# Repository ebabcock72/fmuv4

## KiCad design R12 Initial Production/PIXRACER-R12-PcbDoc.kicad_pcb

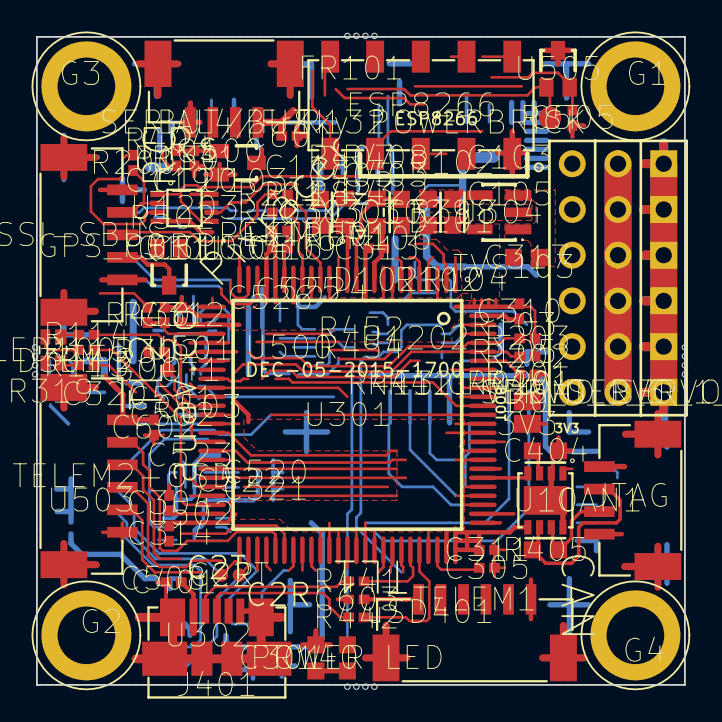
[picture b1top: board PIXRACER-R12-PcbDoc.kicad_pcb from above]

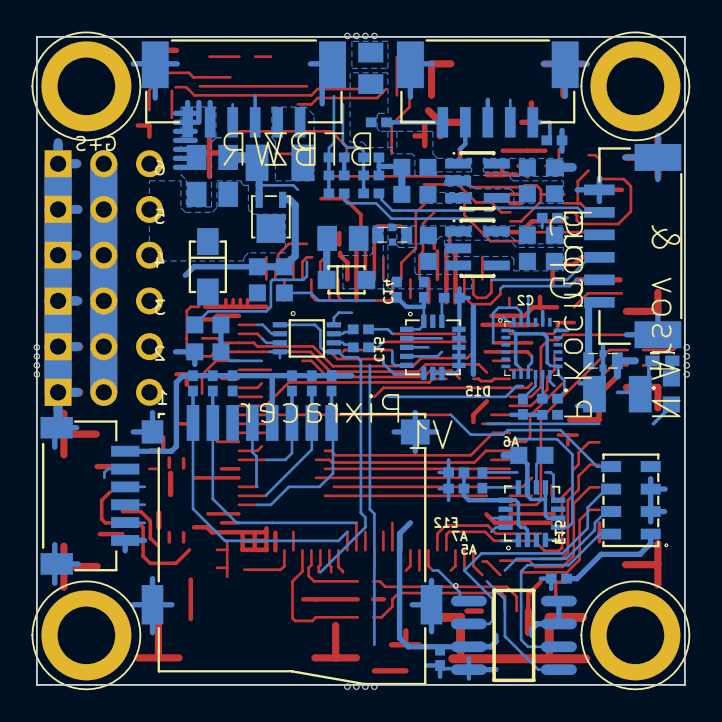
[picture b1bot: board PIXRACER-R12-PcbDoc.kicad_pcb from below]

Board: 4 copper layers, 36.0 x 36.0 mm, 134 parts (66 on the bottom side), 127 nets.

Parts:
3V3: 3V3; PAD1
B0: B0; PAD1
BOOT1: BOOT1; PAD1
BUT/BUZ: BUT/BUZ; Molex_Clik_1.25_5H
C2R: C2R; PAD1
C2T: C2T; PAD1
C103: C103; 0805A
C105: C105; 0805A
C118: C118; 0603A
C119: C119; 0603A
C120: C120; 0603A
C301: C301; 0402A
C302: C302; 0603A
C303: C303; 0603A
C304: C304; 0402A
C305: C305; 0402A
C310: C310; 0402A
C311: C311; 0402A
C312: C312; 0402A
C313: C313; 0402A
C314: C314; 0402A
C315: C315; 0402A
C316: C316; 0402A
C317: C317; 0603A
C319: C319; 0603A
C320: C320; 1206A
C401: C401; 0402A
C402: C402; 0402A
C403: C403; 0402A
C404: C404; 0603A
C405: C405; 0402A
C501: C501; 0402A
C502: C502; 0402A
C503: C503; 0402A
C505: C505; 0402A
C508: C508; 0402A
C509: C509; 0603A
C510: C510; 0603A
C511: C511; 0603A
C520: C520; 0402A
C521: C521; 0402A
C522: C522; 0402A
C523: C523; 0603A
C524: C524; 0402A
C525: C525; 0402A
C526: C526; 0402A
C601: C601; 0402A
C602: C602; 0402A
C603: C603; 0402A
CAN1: CAN1; Molex_1.25_click_4
D101: D101; pmeg2020cp
D102: D102; SOD323F
D301: D301; SOD-523
EMI201: EMI201; EMI_KNH16_0603
EMI501: EMI501; EMI_KNH16_0603
ESP8266: ESP8266; 2.54MM_10PIN_SMD
FR101: FR101; 0805A
FR102: FR102; 1206A
FR106: FR106; 0805A
G1: G1; SMT_PAD_ROUND
G2: G2; SMT_PAD_ROUND
G3: G3; SMT_PAD_ROUND
G4: G4; SMT_PAD_ROUND
GND_SERVO_1_6: GND_SERVO_1_6; HDR1X6
GPS_PORT: GPS_PORT; Molex_Clok_1.25_6H
J401: J401; USBmicro_B
JTAG: JTAG; SM06B-SRSH-TB
LED100: LED100; LTST-C19HE1WT
POWER LED: POWER LED; 0603A
POWERBRICK: POWERBRICK; Molex_Clok_1.25_6H
PPM-RSSI-SBUS-SPEKTRUM: PPM-RSSI-SBUS-SPEKTRUM; Molex_Clik_1.25_5H
Q100: Q100; 2N7002-SOT323
Q101: Q101; 2N7002-SOT323
R102: R102; 0603A
R103: R103; 0603A
R104: R104; 0603A
R105: R105; 0603A
R113: R113; 0402A
R114: R114; 0402A
R115: R115; 0402A
R118: R118; 0603A
R130: R130; 0402A
R131: R131; 0402A
R132: R132; 0402A
R140: R140; 0603A
R200: R200; 0402A
R201: R201; 0402A
R202: R202; 0402A
R203: R203; 0402A
R301: R301; 0402A
R302: R302; 0402A
R318: R318; 0603A
R319: R319; 0603A
R401: R401; 0402A
R403: R403; 0402A
R404: R404; 0402A
R405: R405; 0603A
R407: R407; 0402A
R408: R408; 0402A
R410: R410; 0402A
R411: R411; 0402A
R412: R412; 0402A
R413: R413; 0402A
R422: R422; 0402A
R423: R423; 0402A
R430: R430; 0402A
R431: R431; 0402A
R441: R441; 0402A
R442: R442; 0402A
R452: R452; 0402A
R454: R454; 0402A
R502: R502; 0402A
RST: RST; PAD1
SERIAL4/FrSky: SERIAL4/FrSky; Molex_1.25_click_4
SERVO_1_6: SERVO_1_6; HDR1X6
TELEM1: TELEM1; Molex_Clok_1.25_6H
TELEM2+OSD: TELEM2+OSD; Molex_Clok_1.25_6H
TVS103: TVS103; SOD123F
U10: U10; 8DFN_3x3
U103: U103; SOT23-5
U301: U301; LQFP100_L
U302: U302; SO-8_N
U304: U304; SOT23-5
U500: U500; HCLGA-16L
U501: U501; MPU6500-9250
U502: U502; HMC5883L
U503: U503; MS5611
U504: U504; SOT23-5
U505: U505; SOT-323
U1202: U1202; DCU(SM-8)
U1203: U1203; DCU(SM-8)
VDD_SERVO_1_6: VDD_SERVO_1_6; HDR1X6
X301: X301; Crystal_2.5x2
uSD401: uSD401; MicroSD_China_01

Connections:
8266_CTS: ESP8266.10, U301.41
8266_GPIO0: ESP8266.6, U301.1
8266_GPIO2: ESP8266.4, U301.90
8266_PD: ESP8266.3, U301.4
8266_RST: ESP8266.5, U301.5
8266_RTS: ESP8266.9, U301.67
20608_CS: U301.9, U500.5
20608_DRDY: U301.8, U500.6
ALARM: R130.2, U301.77
BARO_CS: U301.88, U503.5
BATT_CURRENT_SENS: R422.1, U301.26
BATT_VOLT_SENS: R423.1, U301.25
BOOT0: B0.1, R301.1, U301.94
BUZZER+: BUT/BUZ.5, R132.1
BUZZER-: BUT/BUZ.4, Q100.1
CAN1_RX: U10.4, U301.81
CAN1_TX: U10.1, U301.82
CAN2_RX: C2R.1, U301.51
CAN2_TX: C2T.1, U301.52
FMU_CH1: SERVO_1_6.1, U301.45
FMU_CH2: SERVO_1_6.2, U301.44
FMU_CH3: SERVO_1_6.3, U301.42
FMU_CH4: SERVO_1_6.4, U301.40
FMU_CH5: SERVO_1_6.5, U301.60
FMU_CH6: SERVO_1_6.6, U301.61
FMU_I2C1_SCL: GPS_PORT.4, R202.2, U301.95
FMU_I2C1_SDA: GPS_PORT.5, R203.2, U301.96
FMU_LED_BLUE: R113.1, U301.89
FMU_LED_GREEN: R114.1, U301.36
FMU_LED_RED: R115.1, U301.48
FMU_RC_INPUT: U301.35, U301.64, U1203.7
FMU_RC_OUTPUT: U301.63, U1203.6
FMU_SWCLK: JTAG.5, U301.76
FMU_SWDIO: JTAG.4, U301.72
FMU_UART7_RX: JTAG.3, U301.38
FMU_UART7_TX: JTAG.2, U301.39
FMU_USART1_RX: ESP8266.1, U301.93
FMU_USART1_TX: ESP8266.8, U301.92
FMU_USART2_CTS: TELEM1.4, U301.84
FMU_USART2_RTS: TELEM1.5, U301.85
FMU_USART2_RX: TELEM1.3, U301.87
FMU_USART2_TX: TELEM1.2, U301.86
FMU_USART3_CTS: TELEM2+OSD.4, U301.58
FMU_USART3_RTS: TELEM2+OSD.5, U301.59
FMU_USART3_RX: TELEM2+OSD.3, U301.56
FMU_USART3_TX: TELEM2+OSD.2, U301.55
FMU_USART4_RX: GPS_PORT.3, U301.24
FMU_USART4_TX: GPS_PORT.2, U301.23
FMU_USART8_RX: U301.97, U1202.3
FMU_USART8_TX: U301.98, U1202.2
FMU_VBAT: C320.2, D301.2, U301.6
FMU_VDD_3V3: 3V3.1, BUT/BUZ.3, C301.2, C310.2, C311.2, C312.2, C313.2, C314.2, C315.2, C316.2, C319.2, C402.1, C505.2, JTAG.1, LED100.4, R202.1, R203.1, R318.2, R319.1, R401.2, R410.2, R411.2, R412.2, R413.2, U10.5, U301.11, U301.19, U301.21, U301.22, U301.28, U301.50, U301.75, U301.100, U302.3, U302.7, U302.8, U304.5, U505.2, U1202.8, U1203.8, uSD401.4
FRAM_CS: U301.57, U302.1
FRAM_MISO: U301.53, U302.2, U503.6
FRAM_MOSI: U301.54, U302.5, U503.7
FRAM_SCK: U301.47, U302.6, U503.8
FRSKY_IN: R454.1, SERIAL4/FrSky.3
FRSKY_INV: U301.69, U1202.1, U1202.5
FRSKY_OUT: R452.1, SERIAL4/FrSky.2
GND: BUT/BUZ.GND, C103.1, C105.1, C118.1, C119.1, C120.1, C301.1, C302.1, C303.1, C304.2, C305.2, C310.1, C311.1, C312.1, C313.1, C314.1, C315.1, C316.1, C317.1, C319.1, C320.1, C401.1, C402.2, C403.2, C404.1, C405.2, C501.1, C502.1, C503.1, C505.1, C508.1, C509.1, C510.1, C511.1, C520.1, C521.1, C523.1, C524.1, C525.1, C526.1, C601.2, C602.2, C603.2, CAN1.4, CAN1.GND, EMI201.3, EMI201.4, EMI501.3, EMI501.4, ESP8266.2, G1.1, G2.1, G3.1, G4.1, GND_SERVO_1_6.1, GND_SERVO_1_6.2, GND_SERVO_1_6.3, GND_SERVO_1_6.4, GND_SERVO_1_6.5, GND_SERVO_1_6.6, GPS_PORT.6, GPS_PORT.GND, J401.5, J401.6, J401.7, JTAG.6, JTAG.GND, POWERBRICK.5, POWERBRICK.6, POWERBRICK.GND, PPM-RSSI-SBUS-SPEKTRUM.5, PPM-RSSI-SBUS-SPEKTRUM.GND, Q100.2, R104.1, R105.2, R118.1, R131.2, R140.1, R301.2, R302.1, R318.1, R404.2, R407.2, R408.2, R431.2, R502.1, SERIAL4/FrSky.4, SERIAL4/FrSky.GND, TELEM1.6, TELEM1.GND, TELEM2+OSD.6, TELEM2+OSD.GND, TVS103.1, U10.2, U10.8, U10.EP, U103.2, U301.10, U301.20, U301.27, U301.74, U301.99, U302.4, U304.2, U500.7, U500.8, U500.9, U500.10, U500.11, U500.12, U500.13, U500.15, U501.11, U501.18, U501.20, U502.6, U502.9, U502.11, U503.2, U503.3, U504.2, U505.3, U1202.4, U1203.4, X301.2, X301.4, uSD401.6, uSD401.GND
HMC5983_CS: U301.46, U502.4
HMC5983_DRDY: U301.43, U502.15
LED_SAFETY: R403.2, U301.18
MPU9250_CS: U301.17, U501.22
MPU9250_DRDY: U301.62, U501.12
MPU9250_MISO: U301.31, U500.4, U501.9, U502.5
MPU9250_MOSI: U301.32, U500.3, U501.24, U502.16
MPU9250_SCK: U301.30, U500.2, U501.23, U502.1
NetBOOT1_1: BOOT1.1, R302.2, U301.37
NetBUT/BUZ_2: BUT/BUZ.2, R403.1
NetC103_2: C103.2, D101.1, FR102.2, R103.1
NetC304_1: C304.1, U301.49
NetC305_1: C305.1, U301.73
NetC403_1: C403.1, POWERBRICK.3, R408.1, R422.2
NetC405_1: C405.1, POWERBRICK.4, R407.1, R423.2
NetC503_2: C503.2, U501.10
NetC509_2: C509.2, EMI501.2, U504.1
NetC522_1: C522.1, U502.12
NetC522_2: C522.2, U502.8
NetC523_2: C523.2, U502.10
NetC526_2: C526.2, U500.14
NetCAN1_2: CAN1.2, R405.1, U10.7
NetCAN1_3: CAN1.3, R405.2, U10.6
NetD102_2: D102.2, FR106.1
NetD301_1: D301.1, R319.2
NetEMI201_2: EMI201.2, GPS_PORT.1
NetJ401_2: J401.2, R441.1
NetJ401_3: J401.3, R442.1
NetLED100_1: LED100.1, R115.2
NetLED100_2: LED100.2, R114.2
NetLED100_3: LED100.3, R113.2
NetPOWER LED_2: POWER LED.2, R140.2
NetPPM-RSSI-SBUS-SPEKTRUM_3: PPM-RSSI-SBUS-SPEKTRUM.3, R201.1
NetQ100_3: Q100.3, R130.1, R131.1
NetR200_1: R200.1, U1203.3
NetR452_2: R452.2, U1202.7
NetR454_2: R454.2, U1202.6
OSC_IN: C302.2, U301.12, X301.3
OSC_OUT: C303.2, U301.13, X301.1
OTG_FS_DM: R441.2, U301.70
OTG_FS_DP: R442.2, U301.71
RC_INPUT: PPM-RSSI-SBUS-SPEKTRUM.2, R200.2, U1203.2
RSSI_IN: R201.2, U301.16
RST: RST.1, U301.14, U505.1
SAFETY_SWITCH_IN: BUT/BUZ.1, R404.1, U301.33
SBUS_INV: U301.7, U1203.1, U1203.5
SDIO_CK: U301.80, uSD401.5
SDIO_CMD: R411.1, U301.83, uSD401.3
SDIO_D0: R410.1, U301.65, uSD401.7
SDIO_D1: R401.1, U301.66, uSD401.8
SDIO_D2: R413.1, U301.78, uSD401.1
SDIO_D3: R412.1, U301.79, uSD401.2
SPEKTRUM_POWER: Q101.3, U301.3
VBUS: C401.2, D101.2, J401.1, R102.2, R104.2, U301.68
VBUS_VALID: R102.1, U301.15
VDD_3V3_PERIPH: C119.2, C120.2, ESP8266.7, Q101.2, U103.5
VDD_3V3_PERIPH_EN: R118.2, U103.3, U301.34
VDD_3V3_SENSORS: C501.2, C502.2, C508.2, C510.2, C511.2, C520.2, C521.2, C524.2, C525.2, R502.2, U500.1, U500.16, U501.1, U501.8, U501.13, U502.2, U502.13, U503.1, U504.5
VDD_3V3_SENSORS_EN: U301.2, U504.3
VDD_3V3_SPEKTRUM: PPM-RSSI-SBUS-SPEKTRUM.4, Q101.1
VDD_5V_BRICK: FR102.1, POWERBRICK.1, POWERBRICK.2
VDD_5V_IN: C105.2, C118.2, C317.2, D101.3, D102.1, EMI501.1, FR101.1, POWER LED.1, R132.2, R430.2, TVS103.2, U103.1, U304.1, U304.3
VDD_5V_PERIPH: C404.2, C601.1, C602.1, C603.1, CAN1.1, EMI201.1, FR101.2, SERIAL4/FrSky.1, TELEM1.1, TELEM2+OSD.1, U10.3
VDD_5V_RECEIVER: FR106.2, PPM-RSSI-SBUS-SPEKTRUM.1
VDD_5V_SENS: R430.1, R431.1, U301.29
VDD_BRICK_VALID: R103.2, R105.1, U301.91
VDD_SERVO: VDD_SERVO_1_6.1, VDD_SERVO_1_6.2, VDD_SERVO_1_6.3, VDD_SERVO_1_6.4, VDD_SERVO_1_6.5, VDD_SERVO_1_6.6

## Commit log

2018-12-25 converted to kicad
